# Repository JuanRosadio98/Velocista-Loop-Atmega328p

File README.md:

# Velocista-Loop-Atmega328p
Robot Velocista con ATMEGA328P

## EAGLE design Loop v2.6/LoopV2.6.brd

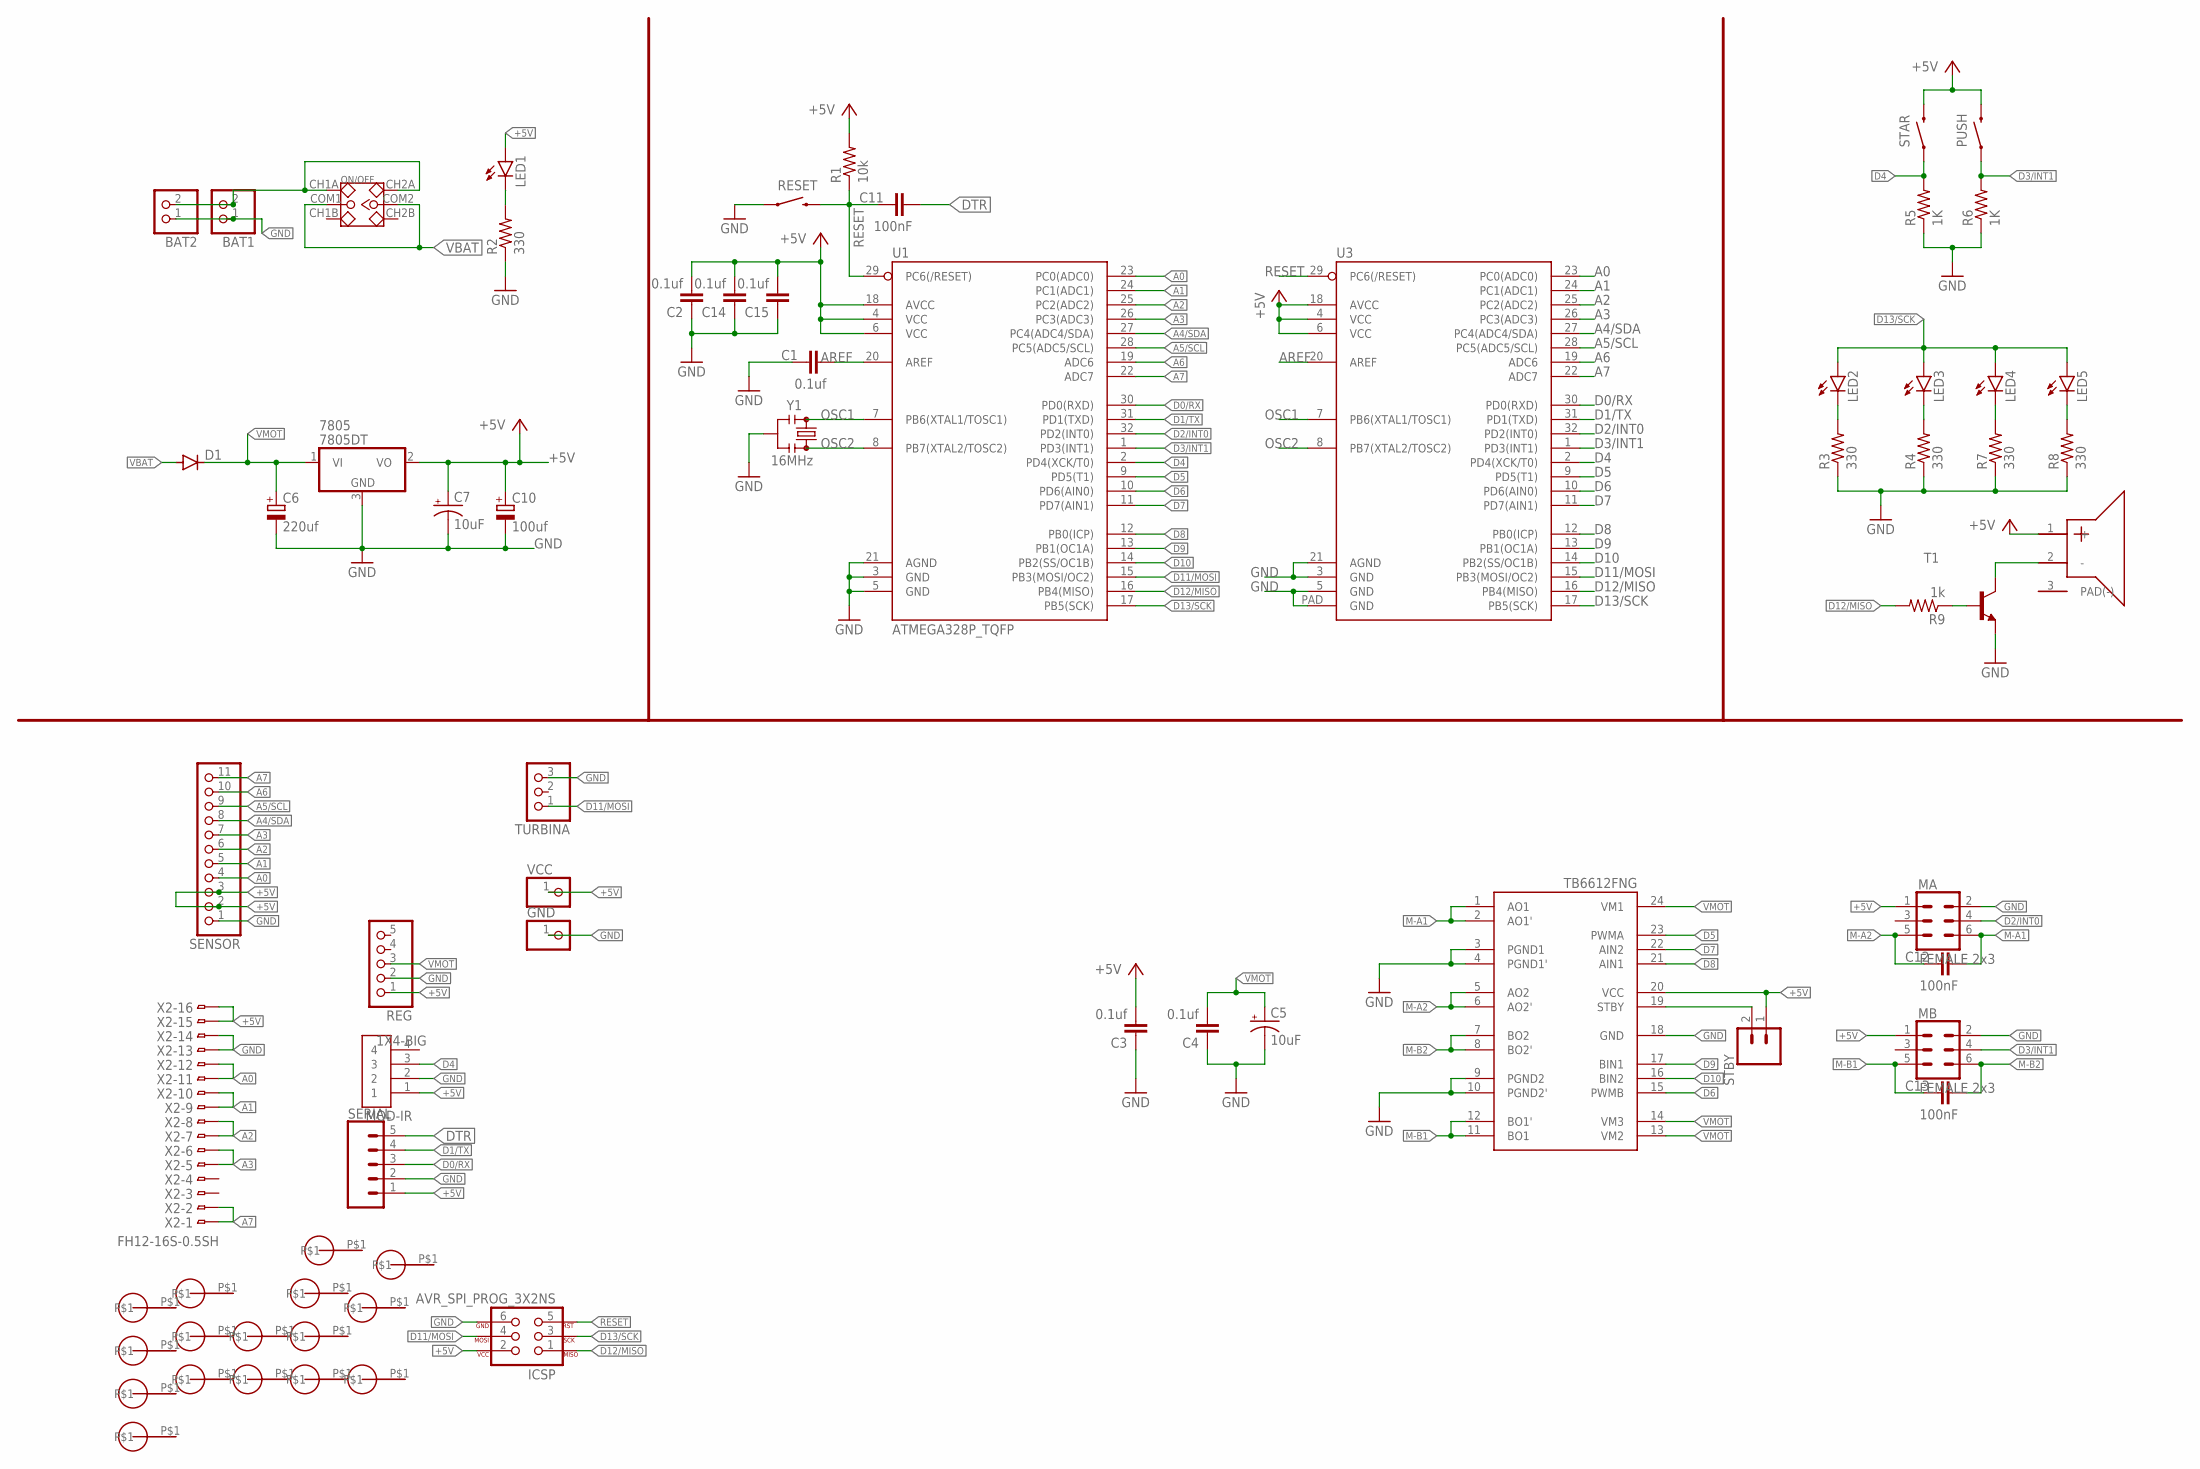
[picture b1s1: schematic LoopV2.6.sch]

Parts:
7805: 7805DT; TO252
BAT1, BAT2: PINHD-1X2; 1X02
C1, C2, C3, C4, C14, C15: 0.1uf; C0805K
C5, C7: 10uF; EIA3216
C6: 220uf; 175TMP-0808
C10: 100uf; 153CLV-0605
C11, C12, C13: 100nF; C0805K
D1: DIODE-DO214AA; DO214AA
GND: PINHD-1X1CB; 1X01-CLEANBIG
IC1: TB6612FNG; SSOP24
ICSP: AVR_SPI_PROG_3X2NS; 2X3-NS
LED1, LED2, LED3, LED4, LED5: LEDCHIPLED_0805; CHIPLED_0805
MA: FEMALE 2x3; 2X3
MB: FEMALE 2x3; 2X3
MOD-IR: 1X4-BIG; 1X04-BIG
ON/OFF: SWITCH-8.53.5MM-THT; SWITCH-8.5*3.5MM-THT
PUSH: TESTING_SWITCH-MOMENTARY-2SMD; TESTING_TACTILE_SWITCH_SMD
R1: 10k; R0805
R2, R3, R4, R7, R8: 330; R0805
R5, R6: 1K; R0805
R9: 1k; R0805
REG: PINHD-1X5; 1X05
RESET: TESTING_SWITCH-MOMENTARY-2SMD; TESTING_TACTILE_SWITCH_SMD
SENSOR: PINHD-1X11; 1X11
SERIAL: CONN_05; 1X05
STAR: TESTING_SWITCH-MOMENTARY-2SMD; TESTING_TACTILE_SWITCH_SMD
STBY: CONN_02; 1X02
T1: -NPN-SOT23-EBC; SOT23-EBC
TURBINA: PINHD-1X3; 1X03
U1: ATMEGA328P_TQFP; TQFP32-08
U3: ATMEGA328P_MLFMLF32; MLF32-PAD
U$4, U$5, U$6, U$7, U$8, U$9, U$10, U$11, U$12, U$13, U$14, U$15, U$17, U$18, U$19, U$20: PAD2; PAD-2.2MM
U$16: BUZZER-KLJ-5030; BUZZERSMD
VCC: PINHD-1X1CB; 1X01-CLEANBIG
X2: FH12-16S-0.5SH
Y1: 16MHz; RESONATOR-SMD-3.2X1.3

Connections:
+5V: 7805.2 (VO), C2.2, C3.2, C7.+, C10.+, C14.2, C15.2, IC1.20 (VCC), ICSP.2, LED1.A, MA.1, MB.1, MOD-IR.1, PUSH.3 (2), R1.2, REG.1, SENSOR.2, SENSOR.3, SERIAL.1, STAR.3 (2), STBY.1, U1.4 (VCC), U1.6 (VCC), U1.18 (AVCC), U3.4 (VCC), U3.6 (VCC), U3.18 (AVCC), U$16.1 (+), VCC.1, X2.15, X2.16
A0: SENSOR.4, U1.23 (PC0(ADC0)), U3.23 (PC0(ADC0)), X2.11, X2.12
A1: SENSOR.5, U1.24 (PC1(ADC1)), U3.24 (PC1(ADC1)), X2.9, X2.10
A2: SENSOR.6, U1.25 (PC2(ADC2)), U3.25 (PC2(ADC2)), X2.7, X2.8
A3: SENSOR.7, U1.26 (PC3(ADC3)), U3.26 (PC3(ADC3)), X2.5, X2.6
A4/SDA: SENSOR.8, U1.27 (PC4(ADC4/SDA)), U3.27 (PC4(ADC4/SDA))
A5/SCL: SENSOR.9, U1.28 (PC5(ADC5/SCL)), U3.28 (PC5(ADC5/SCL))
A6: SENSOR.10, U1.19 (ADC6), U3.19 (ADC6)
A7: SENSOR.11, U1.22 (ADC7), U3.22 (ADC7), X2.1, X2.2
AREF: C1.2, U1.20 (AREF), U3.20 (AREF)
D0/RX: SERIAL.3, U1.30 (PD0(RXD)), U3.30 (PD0(RXD))
D1/TX: SERIAL.4, U1.31 (PD1(TXD)), U3.31 (PD1(TXD))
D2/INT0: MA.4, U1.32 (PD2(INT0)), U3.32 (PD2(INT0))
D3/INT1: MB.4, PUSH.1, R6.2, U1.1 (PD3(INT1)), U3.1 (PD3(INT1))
D4: MOD-IR.3, R5.2, STAR.1, U1.2 (PD4(XCK/T0)), U3.2 (PD4(XCK/T0))
D5: IC1.23 (PWMA), U1.9 (PD5(T1)), U3.9 (PD5(T1))
D6: IC1.15 (PWMB), U1.10 (PD6(AIN0)), U3.10 (PD6(AIN0))
D7: IC1.22 (AIN2), U1.11 (PD7(AIN1)), U3.11 (PD7(AIN1))
D8: IC1.21 (AIN1), U1.12 (PB0(ICP)), U3.12 (PB0(ICP))
D9: IC1.17 (BIN1), U1.13 (PB1(OC1A)), U3.13 (PB1(OC1A))
D10: IC1.16 (BIN2), U1.14 (PB2(SS/OC1B)), U3.14 (PB2(SS/OC1B))
D11/MOSI: ICSP.4, TURBINA.1, U1.15 (PB3(MOSI/OC2)), U3.15 (PB3(MOSI/OC2))
D12/MISO: ICSP.1, R9.2, U1.16 (PB4(MISO)), U3.16 (PB4(MISO))
D13/SCK: ICSP.3, LED2.A, LED3.A, LED4.A, LED5.A, U1.17 (PB5(SCK)), U3.17 (PB5(SCK))
DTR: C11.2, SERIAL.5
GND: 7805.3 (GND), BAT1.1, BAT2.1, C1.1, C2.1, C3.1, C4.1, C5.-, C6.-, C7.-, C10.-, C14.1, C15.1, GND.1, IC1.3 (PGND1), IC1.4 (PGND1'), IC1.9 (PGND2), IC1.10 (PGND2'), IC1.18 (GND), ICSP.6, MA.2, MB.2, MOD-IR.2, R2.1, R3.1, R4.1, R5.1, R6.1, R7.1, R8.1, REG.2, RESET.1, SENSOR.1, SERIAL.2, T1.E, TURBINA.3, U1.3 (GND), U1.5 (GND), U1.21 (AGND), U3.3 (GND), U3.5 (GND), U3.21 (AGND), U3.PAD (GND), X2.13, X2.14, Y1.2
M-A1: C12.2, IC1.1 (AO1), IC1.2 (AO1'), MA.6
M-A2: C12.1, IC1.5 (AO2), IC1.6 (AO2'), MA.5
M-B1: C13.1, IC1.11 (BO1), IC1.12 (BO1'), MB.5
M-B2: C13.2, IC1.7 (BO2), IC1.8 (BO2'), MB.6
unnamed: LED1.C, R2.2
unnamed: T1.C, U$16.2 (-)
unnamed: LED4.C, R7.2
unnamed: LED2.C, R3.2
unnamed: LED3.C, R4.2
unnamed: LED5.C, R8.2
unnamed: R9.1, T1.B
unnamed: IC1.19 (STBY), STBY.2
unnamed: BAT1.2, BAT2.2, ON/OFF.CH1A, ON/OFF.CH2A
OSC1: U1.7 (PB6(XTAL1/TOSC1)), U3.7 (PB6(XTAL1/TOSC1)), Y1.1
OSC2: U1.8 (PB7(XTAL2/TOSC2)), U3.8 (PB7(XTAL2/TOSC2)), Y1.3
RESET: C11.1, ICSP.5, R1.1, RESET.3 (2), U1.29 (PC6(/RESET)), U3.29 (PC6(/RESET))
VBAT: D1.A, ON/OFF.COM1, ON/OFF.COM2
VMOT: 7805.1 (VI), C4.2, C5.+, C6.+, D1.C, IC1.13 (VM2), IC1.14 (VM3), IC1.24 (VM1), REG.3

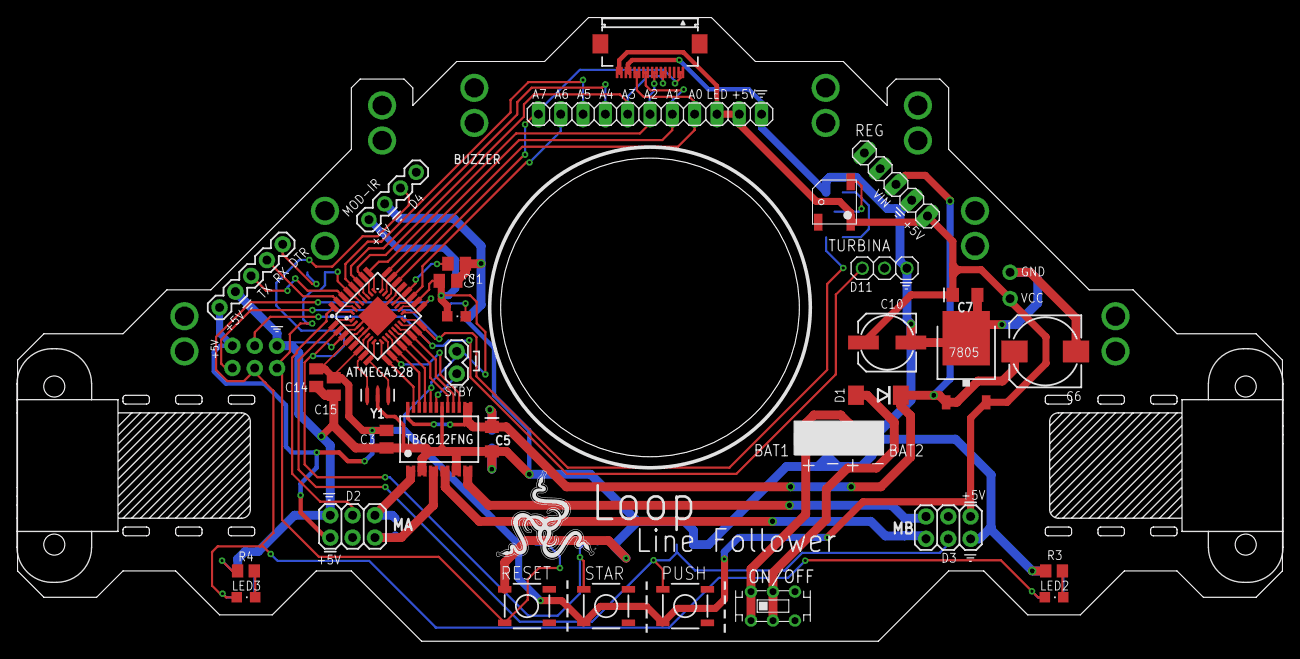
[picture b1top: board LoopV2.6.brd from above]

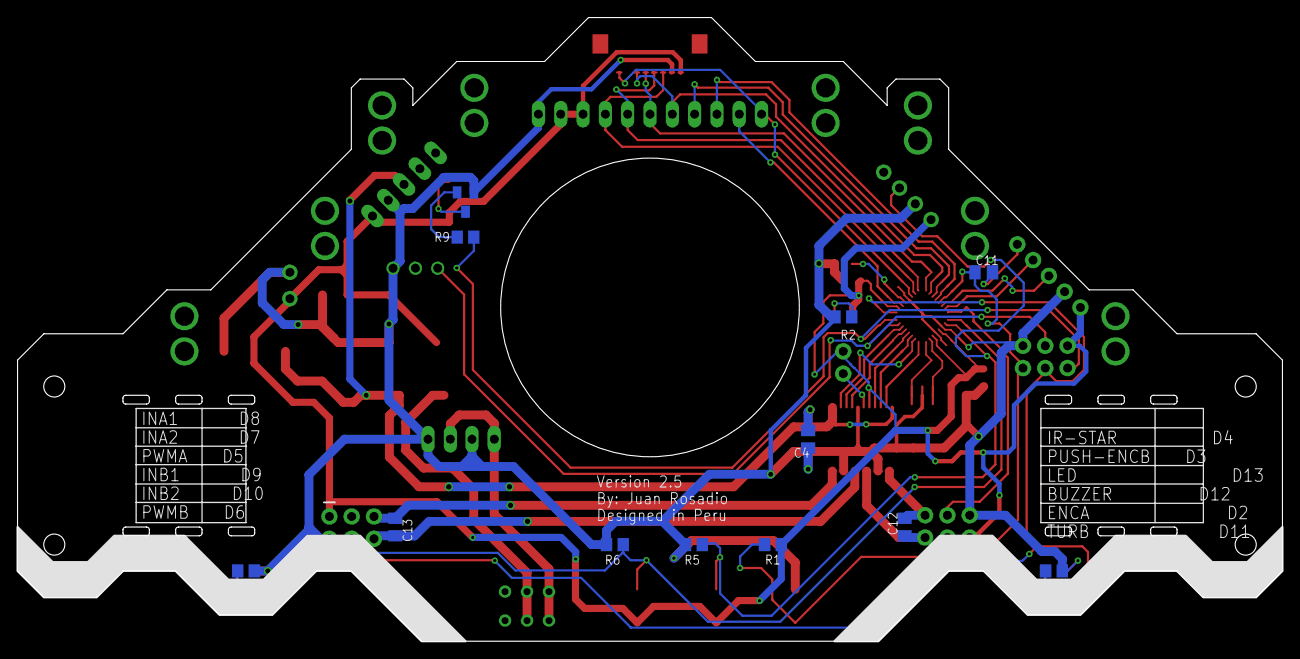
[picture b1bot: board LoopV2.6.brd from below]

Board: 2 copper layers, 143.9 x 70.9 mm, 72 parts (14 on the bottom side), 44 nets.

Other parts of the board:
U$1, U$2: MOTORPOLOLU
U$3: RAZER-1

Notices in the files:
parts and their libraries:
SparkFun-IC-Microcontroller: Licensing: Creative Commons ShareAlike 4.0 International - https://creativecommons.org/licenses/by-sa/4.0
